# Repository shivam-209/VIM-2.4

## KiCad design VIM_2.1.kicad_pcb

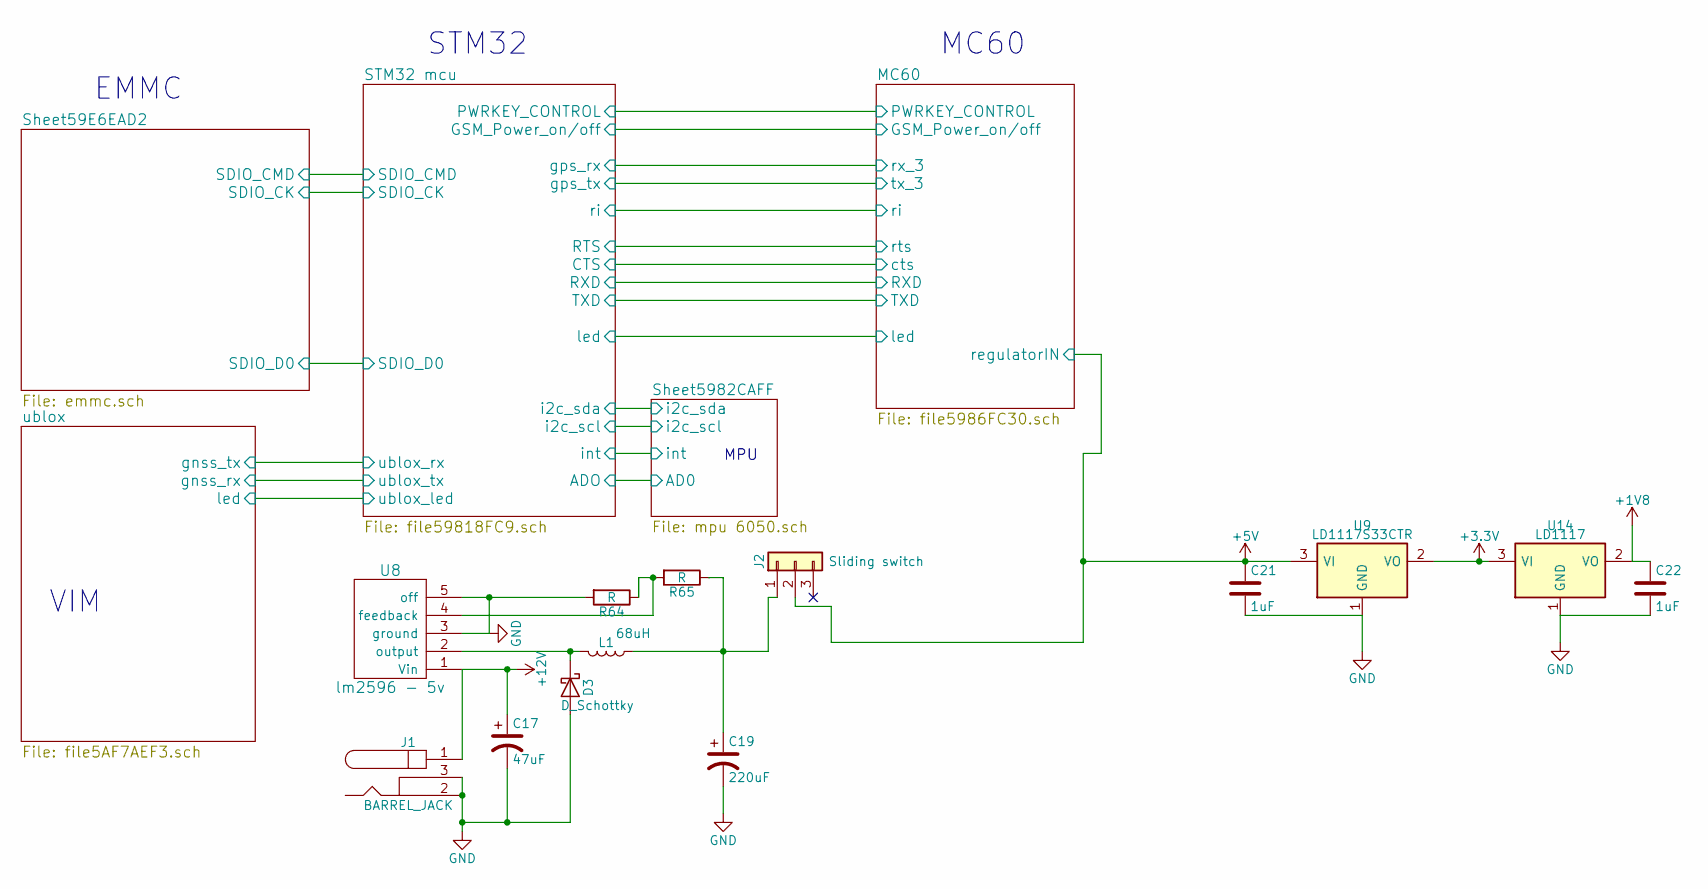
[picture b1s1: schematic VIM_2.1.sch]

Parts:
C17: 47uF; CP_Elec_8x6.7
C19: 220uF; CP_Elec_6.3x5.7
C21, C22: 1uF; C_0603_HandSoldering
D3: D_Schottky; D_SOD-123
J1: BARREL_JACK
J2: Sliding switch; Pin_Header_Straight_1x03_Pitch2.54mm
L1: 68uH; L_7.3x7.3_H3.5
R64, R65: R; R_0603_HandSoldering
U8: lm2596 - 5v; TO-263-5_TabPin3
U9: LD1117S33CTR; SOT-223-3Lead_TabPin2
U14: LD1117; SOT-223-3_TabPin2

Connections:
+1V8: C22.1, U14.2 (VO); also elsewhere on the board
+3V3: U9.2 (VO), U14.3 (VI); also elsewhere on the board
+5V: C21.1, J2.2, U9.3 (VI); also elsewhere on the board
+12V: C17.1, J1.1, U8.1 (Vin); also elsewhere on the board
GND: C17.2, C19.2, C21.2, C22.2, D3.2 (A), J1.2, J1.3, R64.2, U8.3 (ground), U8.5 (off), U9.1 (GND), U14.1 (GND); also elsewhere on the board
unnamed: C19.1, J2.1, L1.1, R65.1
unnamed: D3.1 (K), L1.2, U8.2 (output)
unnamed: R64.1, R65.2, U8.4 (feedback)

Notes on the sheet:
EMMC
STM32
MC60
MPU
VIM

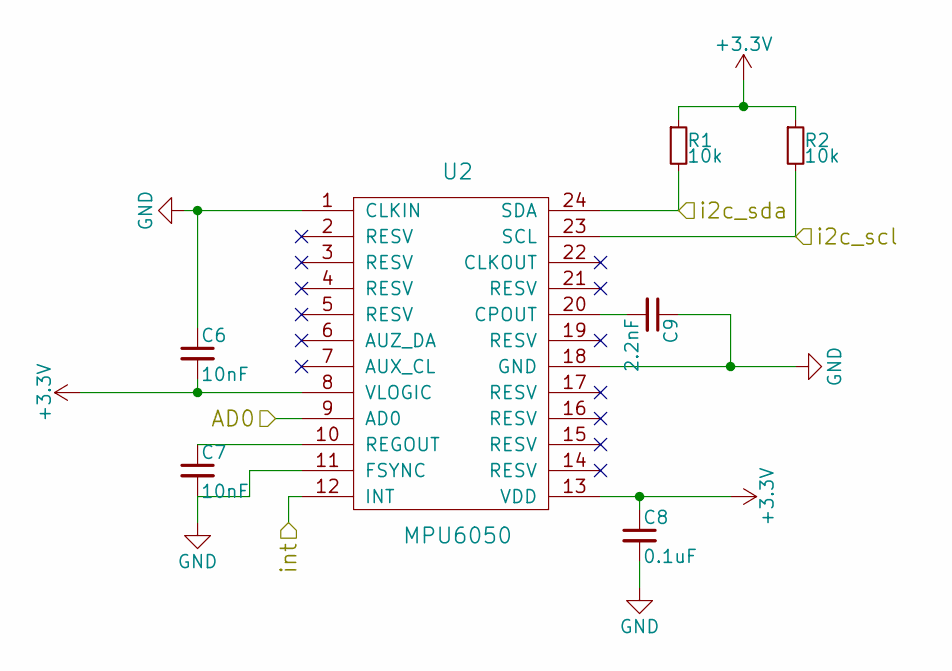
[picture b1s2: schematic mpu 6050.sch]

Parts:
C6, C7: 10nF; C_0603_HandSoldering
C8: 0.1uF; C_0603_HandSoldering
C9: 2.2nF; C_0603_HandSoldering
R1, R2: 10k; R_0603_HandSoldering
U2: MPU6050; QFN-24_4x4mm_Pitch0.5mm

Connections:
+3V3: C6.2, C8.1, R1.1, R2.1, U2.8 (VLOGIC), U2.13 (VDD); also elsewhere on the board
/STM32 mcu/i2c_scl: R2.2, U2.23 (SCL); also elsewhere on the board
/STM32 mcu/i2c_sda: R1.2, U2.24 (SDA); also elsewhere on the board
/STM32 mcu/int: U2.12 (INT); also elsewhere on the board
/Sheet5982CAFF/AD0: U2.9 (AD0); also elsewhere on the board
GND: C6.1, C7.2, C8.2, C9.1, U2.1 (CLKIN), U2.11 (FSYNC), U2.18 (GND); also elsewhere on the board
unnamed: C7.1, U2.10 (REGOUT)
unnamed: C9.2, U2.20 (CPOUT)

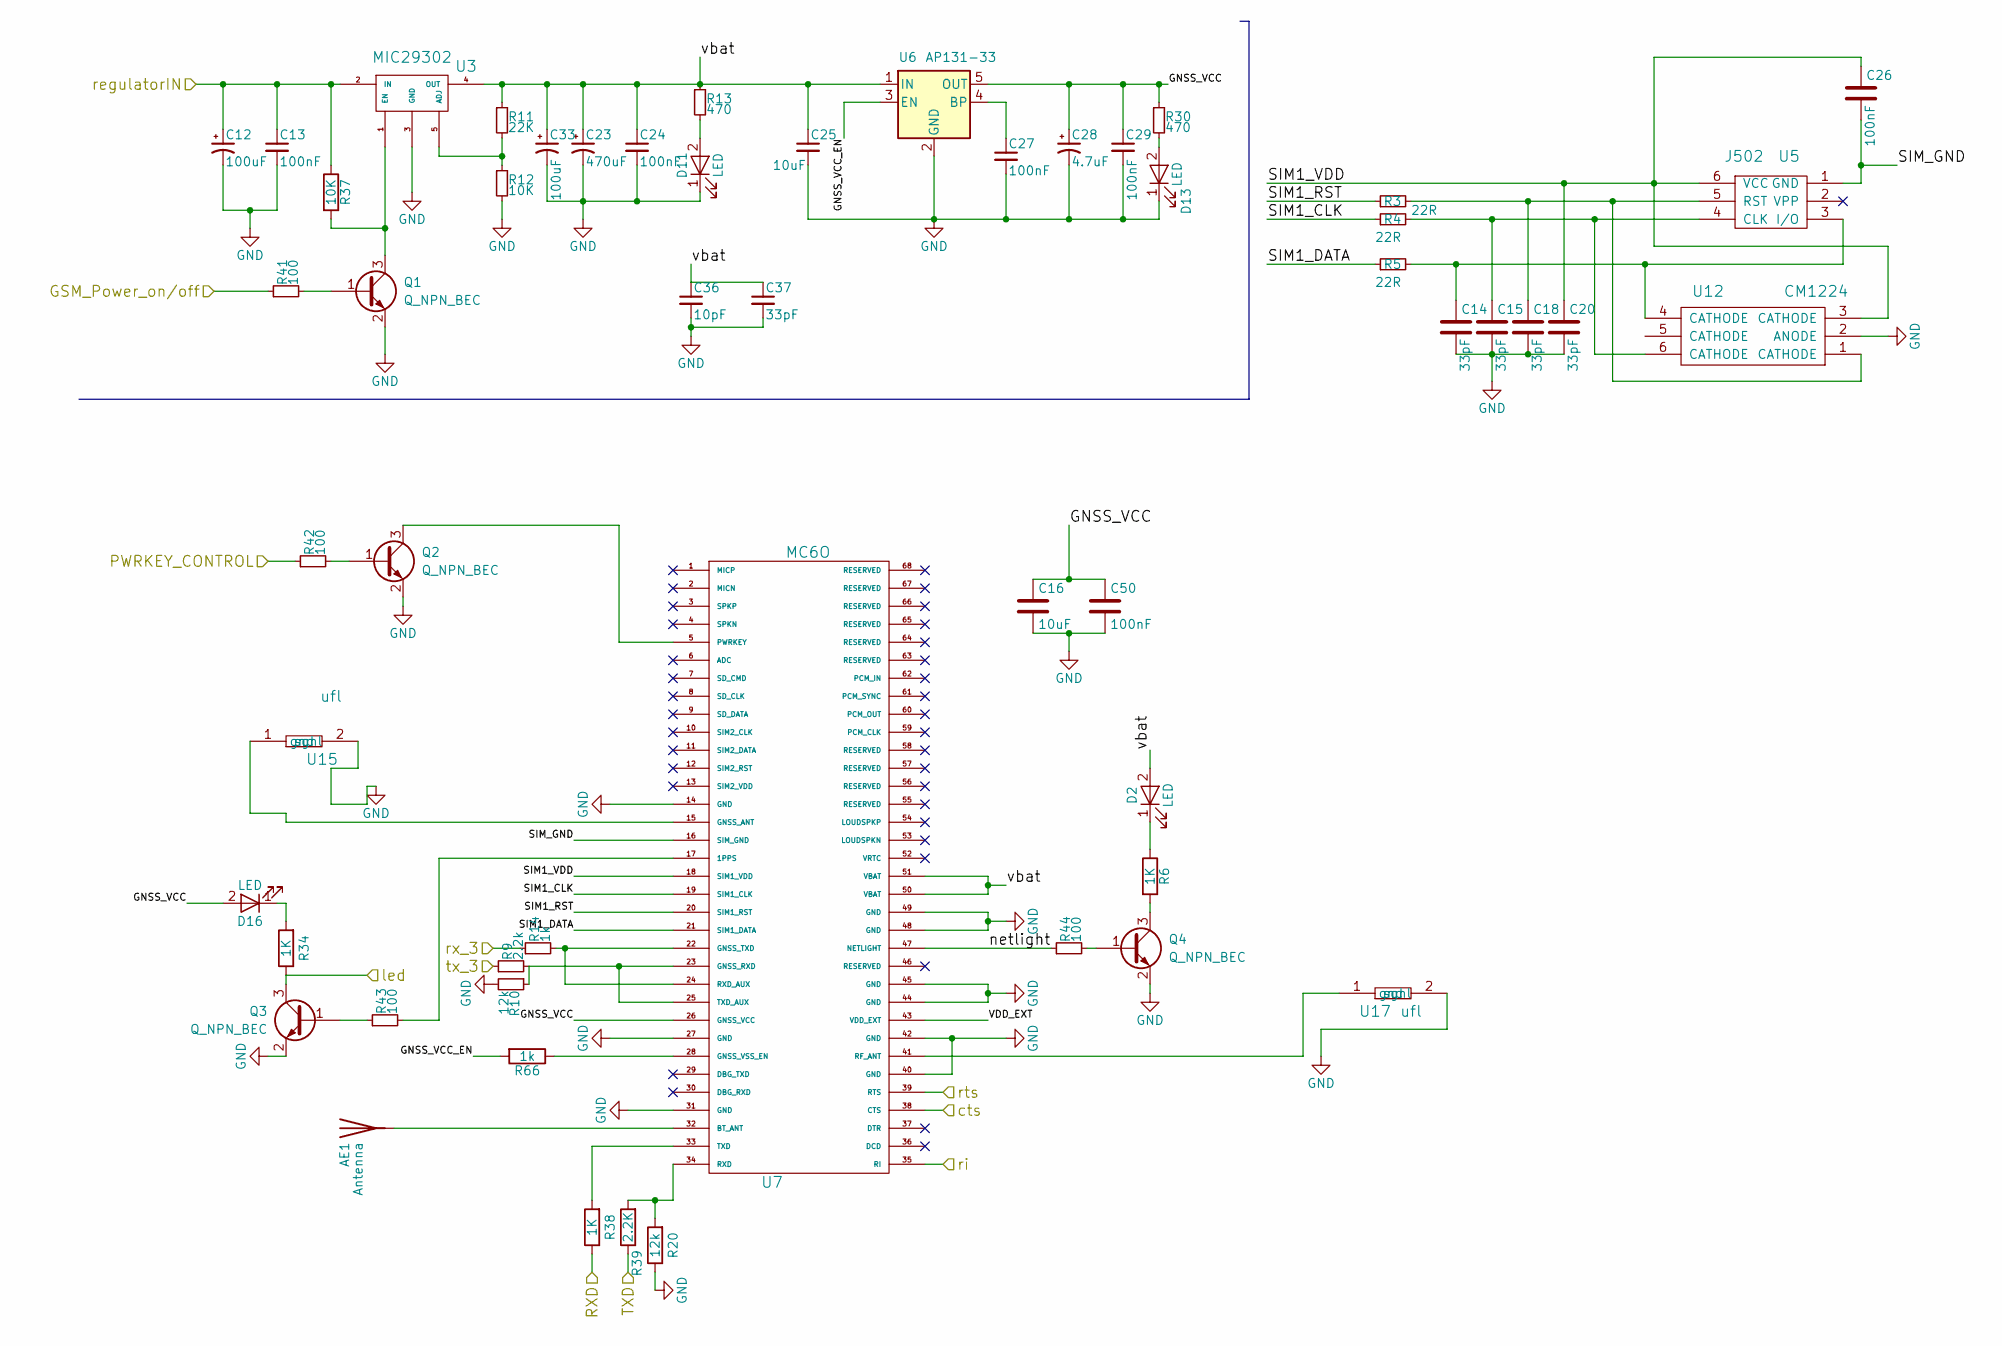
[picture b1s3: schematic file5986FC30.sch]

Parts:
AE1: Antenna; bluetooth_antenna
C12: 100uF; CP_Elec_6.3x5.7
C13, C24, C26, C27, C29, C50: 100nF; C_0603_HandSoldering
C14, C15, C18, C20, C37: 33pF; C_0603_HandSoldering
C16, C25: 10uF; C_0603_HandSoldering
C23: 470uF; CP_Elec_8x10
C28: 4.7uF; CP_Elec_5x5.3
C33: 100uF; CP_Tantalum_Case-D_EIA-7343-31_Reflow
C36: 10pF; C_0603_HandSoldering
D2, D11, D13, D16: LED; LED_0805
Q1, Q2, Q3, Q4: Q_NPN_BEC; SOT-23
R3, R4, R5: 22R; R_0603_HandSoldering
R6, R34, R38: 1K; R_0603_HandSoldering
R9: 2.2k; R_0603_HandSoldering
R10, R20: 12k; R_0603_HandSoldering
R11: 22K; R_0603_HandSoldering
R12, R37: 10K; R_0603_HandSoldering
R13, R30: 470; R_0603_HandSoldering
R14, R66: 1k; R_0603_HandSoldering
R39: 2.2K; R_0603_HandSoldering
R41, R42, R43, R44: 100; R_0603_HandSoldering
U3: MIC29302; TO-263-5_TabPin3
U5: J502; simcardconn
U6: AP131-33; SOT-23-5
U7: MC6O; Quectel_MC-60
U12: CM1224; SOT-23-6
U15, U17: ufl; ufl_shield

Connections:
+5V: C12.1, C13.1, R37.1, U3.2 (IN); also elsewhere on the board
/MC60/GNSS_VCC: C16.1, C28.1, C29.1, C50.1, D16.2 (A), R30.1, U6.5 (OUT), U7.26 (GNSS_VCC)
/MC60/GNSS_VCC_EN: R66.2, U6.3 (EN)
/MC60/GSM_Power_on/off: R41.1; also elsewhere on the board
/MC60/PWRKEY_CONTROL: R42.1; also elsewhere on the board
/MC60/RXD: R38.1; also elsewhere on the board
/MC60/SIM1_CLK: R4.1, U7.19 (SIM1_CLK)
/MC60/SIM1_DATA: R5.1, U7.21 (SIM1_DATA)
/MC60/SIM1_RST: R3.1, U7.20 (SIM1_RST)
/MC60/SIM1_VDD: C20.1, C26.1, U5.6 (VCC), U7.18 (SIM1_VDD), U12.3 (CATHODE)
/MC60/SIM_GND: C26.2, U5.1 (GND), U7.16 (SIM_GND)
/MC60/TXD: R39.1; also elsewhere on the board
/MC60/VDD_EXT: U7.43 (VDD_EXT)
/MC60/led: Q3.3 (C), R34.1; also elsewhere on the board
/MC60/netlight: R44.1, U7.47 (NETLIGHT)
/MC60/ri: U7.35 (RI); also elsewhere on the board
/MC60/vbat: C23.1, C24.1, C25.1, C33.1, C36.1, C37.1, D2.2 (A), R11.1, R13.1, U3.4 (OUT), U6.1 (IN), U7.50 (VBAT), U7.51 (VBAT)
/STM32 mcu/CTS: U7.38 (CTS); also elsewhere on the board
/STM32 mcu/RTS: U7.39 (RTS); also elsewhere on the board
/STM32 mcu/gps_rx: R14.1; also elsewhere on the board
/STM32 mcu/gps_tx: R9.1; also elsewhere on the board
GND: C12.2, C13.2, C14.2, C15.2, C16.2, C18.2, C20.2, C23.2, C24.2, C25.2, C27.2, C28.2, C29.2, C33.2, C36.2, C37.2, C50.2, D11.1 (K), D13.1 (K), Q1.2 (E), Q2.2 (E), Q3.2 (E), Q4.2 (E), R10.2, R12.2, R20.1, U3.3 (GND), U6.2 (GND), U7.14 (GND), U7.27 (GND), U7.31 (GND), U7.40 (GND), U7.42 (GND), U7.44 (GND), U7.45 (GND), U7.48 (GND), U7.49 (GND), U12.2 (ANODE), U15.2 (gnd), U17.2 (gnd); also elsewhere on the board
unnamed: AE1.1, U7.32 (BT_ANT)
unnamed: C14.1, R5.2, U5.3 (I/O), U12.4 (CATHODE)
unnamed: C15.1, R4.2, U5.4 (CLK), U12.6 (CATHODE)
unnamed: C18.1, R3.2, U5.5 (RST), U12.1 (CATHODE)
unnamed: C27.1, U6.4 (BP)
unnamed: D2.1 (K), R6.1
unnamed: D11.2 (A), R13.2
unnamed: D13.2 (A), R30.2
unnamed: D16.1 (K), R34.2
unnamed: Q1.1 (B), R41.2
unnamed: Q1.3 (C), R37.2, U3.1 (EN)
unnamed: Q2.1 (B), R42.2
unnamed: Q2.3 (C), U7.5 (PWRKEY)
unnamed: Q3.1 (B), R43.1
unnamed: Q4.1 (B), R44.2
unnamed: Q4.3 (C), R6.2
unnamed: R9.2, R10.1, U7.23 (GNSS_RXD), U7.25 (TXD_AUX)
unnamed: R11.2, R12.1, U3.5 (ADJ)
unnamed: R14.2, U7.22 (GNSS_TXD), U7.24 (RXD_AUX)
unnamed: R20.2, R39.2, U7.34 (RXD)
unnamed: R38.2, U7.33 (TXD)
unnamed: R43.2, U7.17 (1PPS)
unnamed: R66.1, U7.28 (GNSS_VSS_EN)
unnamed: U7.15 (GNSS_ANT), U15.1 (sgnl)
unnamed: U7.41 (RF_ANT), U17.1 (sgnl)

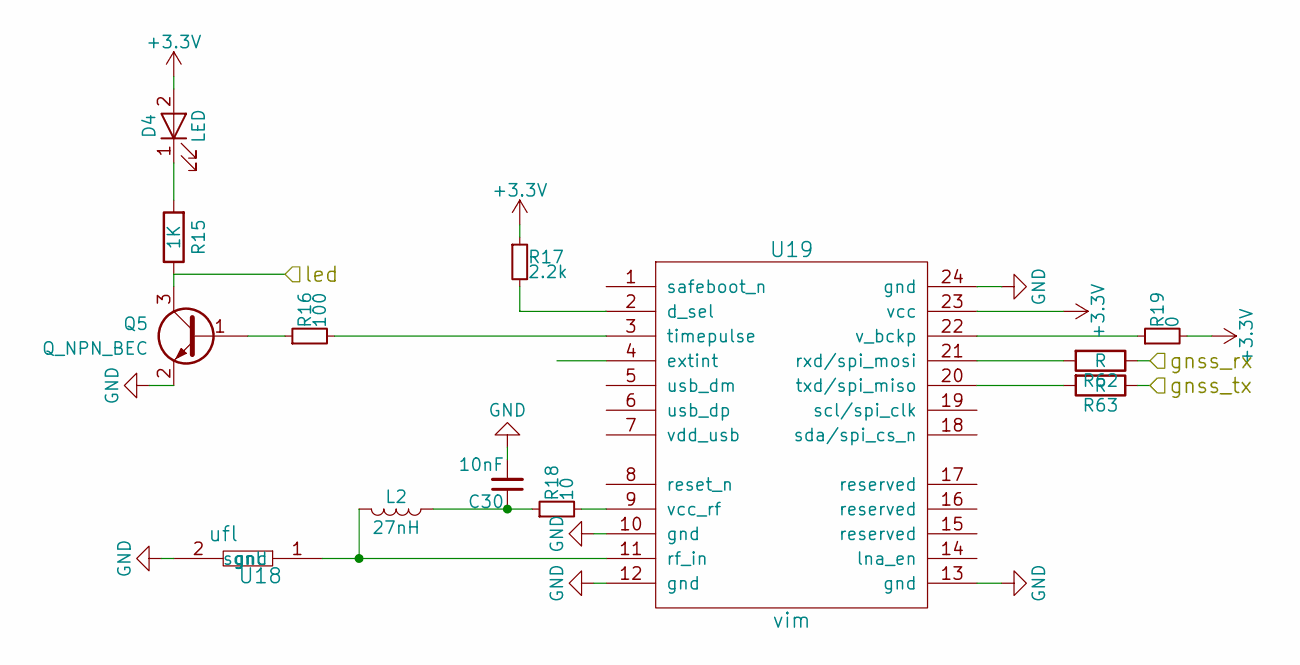
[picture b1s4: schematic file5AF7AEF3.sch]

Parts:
C30: 10nF; C_0603_HandSoldering
D4: LED; LED_0805
L2: 27nH; L_0805
Q5: Q_NPN_BEC; SOT-23
R15: 1K; R_0603_HandSoldering
R16: 100; R_0603_HandSoldering
R17: 2.2k; R_0603_HandSoldering
R18: 10; R_0603_HandSoldering
R19: 0; R_0603_HandSoldering
R62, R63: R; R_0603_HandSoldering
U18: ufl; ufl_shield
U19: vim; MU8

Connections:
+3V3: D4.2 (A), R17.1, R19.2, U19.23 (vcc); also elsewhere on the board
/ublox/gnss_rx: R62.1; also elsewhere on the board
/ublox/gnss_tx: R63.1; also elsewhere on the board
/ublox/led: Q5.3 (C), R15.1; also elsewhere on the board
GND: C30.2, Q5.2 (E), U18.2 (gnd), U19.10 (gnd), U19.12 (gnd), U19.13 (gnd), U19.24 (gnd); also elsewhere on the board
unnamed: C30.1, L2.1, R18.1
unnamed: D4.1 (K), R15.2
unnamed: L2.2, U18.1 (sgnl), U19.11 (rf_in)
unnamed: Q5.1 (B), R16.1
unnamed: R16.2, U19.3 (timepulse)
unnamed: R17.2, U19.2 (d_sel)
unnamed: R18.2, U19.9 (vcc_rf)
unnamed: R19.1, U19.22 (v_bckp)
unnamed: R62.2, U19.21 (rxd/spi_mosi)
unnamed: R63.2, U19.20 (txd/spi_miso)

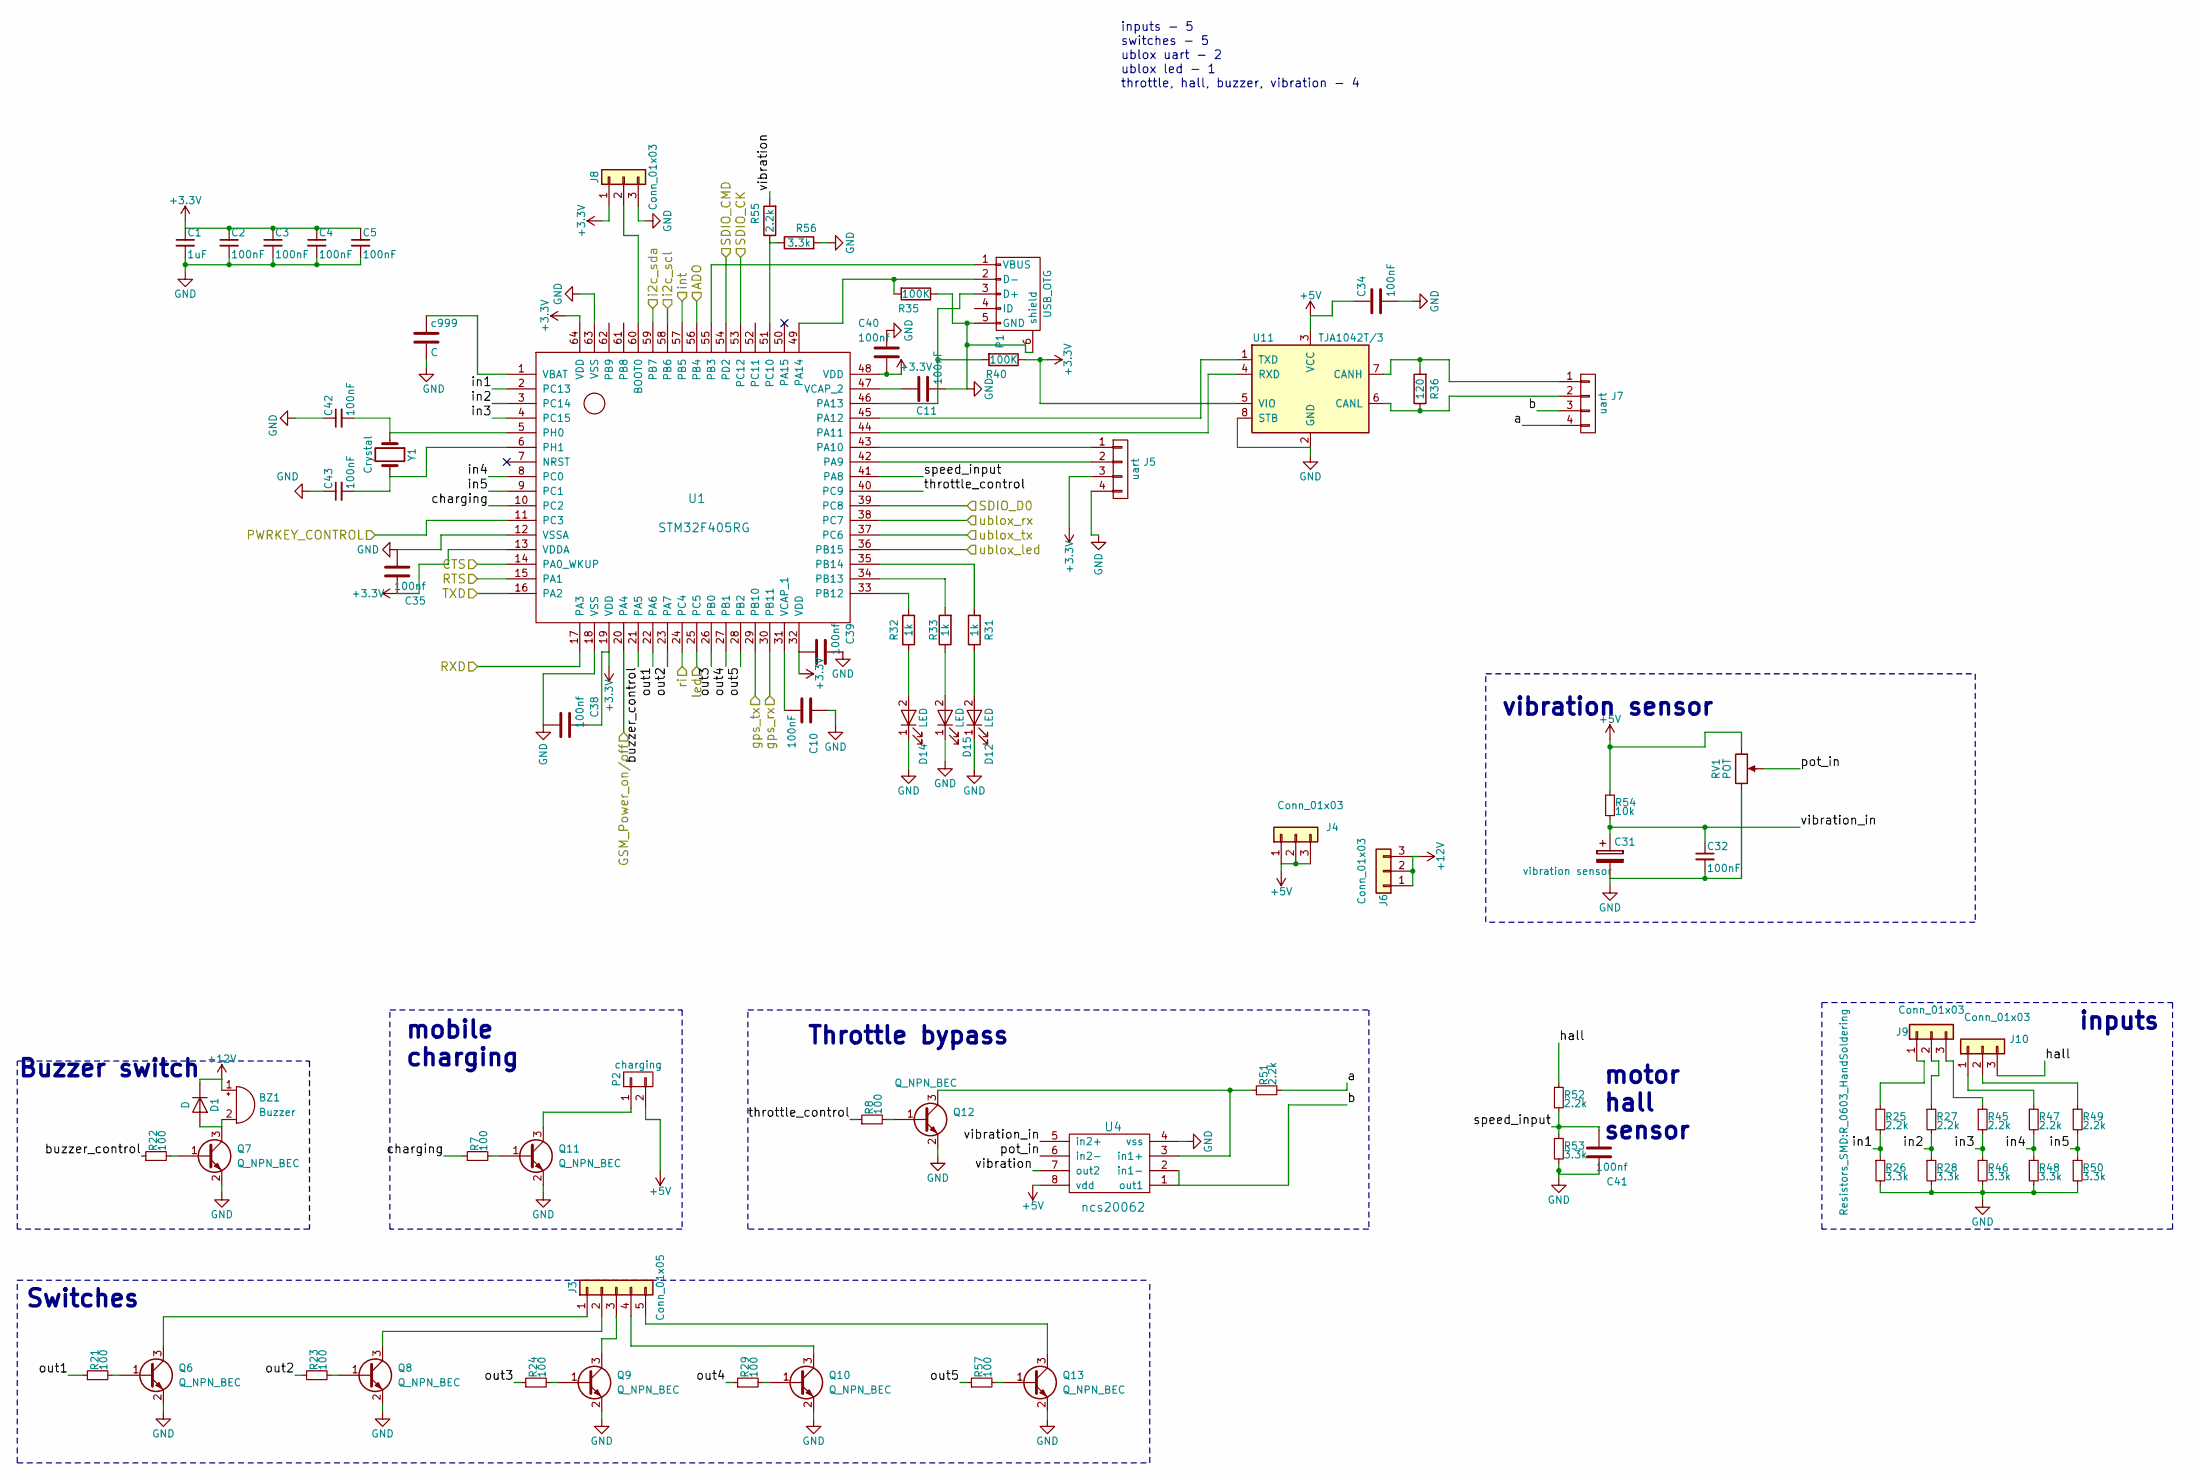
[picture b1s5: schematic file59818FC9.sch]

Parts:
BZ1: Buzzer; Buzzer_12x9.5RM7.6
C1: 1uF; C_0603_HandSoldering
C2, C3, C4, C5, C10, C11, C32, C34, C42, C43: 100nF; C_0603_HandSoldering
C31: vibration sensor; CP_Radial_D5.0mm_P2.50mm
C35, C38, C39, C40, C41: 100nf; C_0603_HandSoldering
D1: D; D_SOD-123
D12, D14, D15: LED; LED_0805
J3: Conn_01x05; Pin_Header_Straight_1x05_Pitch2.54mm
J4, J6, J8, J9, J10: Conn_01x03; Pin_Header_Straight_1x03_Pitch2.54mm
J5, J7: uart; Pin_Header_Straight_1x04_Pitch2.54mm
P1: USB_OTG; USB_Micro-B
P2: charging; Pin_Header_Straight_1x02_Pitch2.54mm
Q6, Q7, Q8, Q9, Q10, Q11, Q12, Q13: Q_NPN_BEC; SOT-23
R7, R8, R21, R22, R23, R24, R29, R57: 100; R_0603_HandSoldering
R25, R27, R45, R47, R49, R51, R52, R55: 2.2k; R_0603_HandSoldering
R26, R28, R46, R48, R50, R53, R56: 3.3k; R_0603_HandSoldering
R31, R32, R33: 1k; R_0603_HandSoldering
R35, R40: 100K; R_0603_HandSoldering
R36: 120; R_0603_HandSoldering
R54: 10k; R_0603_HandSoldering
RV1: POT; Potentiometer_Triwood_RM-065
U1: STM32F405RG; LQFP-64_10x10mm_Pitch0.5mm
U4: ncs20062; SOIC-8_3.9x4.9mm_Pitch1.27mm
U11: TJA1042T/3; SOIC-8_3.9x4.9mm_Pitch1.27mm
Y1: Crystal; Crystal_HC52-8mm_Vertical
c999: C; C_0603_HandSoldering

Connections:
+3V3: C1.1, C2.1, C3.1, C4.1, C5.1, C35.1, C38.1, C39.2, C40.2, J5.3, J8.1, R40.1, U1.13 (VDDA), U1.19 (VDD), U1.32 (VDD), U1.48 (VDD), U1.64 (VDD), U11.5 (VIO); also elsewhere on the board
+5V: C34.1, J4.1, J4.2, J4.3, P2.2, R54.1, RV1.1, U4.8 (vdd), U11.3 (VCC); also elsewhere on the board
+12V: BZ1.1 (-), D1.1 (K), J6.1, J6.2, J6.3; also elsewhere on the board
/MC60/GSM_Power_on/off: U1.20 (PA4); also elsewhere on the board
/MC60/PWRKEY_CONTROL: U1.11 (PC3); also elsewhere on the board
/MC60/RXD: U1.17 (PA3); also elsewhere on the board
/MC60/TXD: U1.16 (PA2); also elsewhere on the board
/MC60/led: U1.25 (PC5); also elsewhere on the board
/MC60/ri: U1.24 (PC4); also elsewhere on the board
/STM32 mcu/CTS: U1.14 (PA0_WKUP); also elsewhere on the board
/STM32 mcu/RTS: U1.15 (PA1); also elsewhere on the board
/STM32 mcu/SDIO_CK: U1.53 (PC12); also elsewhere on the board
/STM32 mcu/SDIO_CMD: U1.54 (PD2); also elsewhere on the board
/STM32 mcu/SDIO_D0: U1.39 (PC8); also elsewhere on the board
/STM32 mcu/a: J7.4, R51.2
/STM32 mcu/b: J7.3, U4.1 (out1), U4.2 (in1-)
/STM32 mcu/buzzer_control: R22.1, U1.21 (PA5)
/STM32 mcu/charging: R7.1, U1.10 (PC2)
/STM32 mcu/gps_rx: U1.30 (PB11); also elsewhere on the board
/STM32 mcu/gps_tx: U1.29 (PB10); also elsewhere on the board
/STM32 mcu/hall: J10.3, R52.1
/STM32 mcu/i2c_scl: U1.58 (PB6); also elsewhere on the board
/STM32 mcu/i2c_sda: U1.59 (PB7); also elsewhere on the board
/STM32 mcu/in1: R25.2, R26.1, U1.2 (PC13)
/STM32 mcu/in2: R27.2, R28.1, U1.3 (PC14)
/STM32 mcu/in3: R45.2, R46.1, U1.4 (PC15)
/STM32 mcu/in4: R47.2, R48.1, U1.8 (PC0)
/STM32 mcu/in5: R49.2, R50.1, U1.9 (PC1)
/STM32 mcu/int: U1.57 (PB5); also elsewhere on the board
/STM32 mcu/out1: R21.1, U1.22 (PA6)
/STM32 mcu/out2: R23.1, U1.23 (PA7)
/STM32 mcu/out3: R24.1, U1.26 (PB0)
/STM32 mcu/out4: R29.1, U1.27 (PB1)
/STM32 mcu/out5: R57.1, U1.28 (PB2)
/STM32 mcu/pot_in: RV1.2, U4.6 (in2-)
/STM32 mcu/speed_input: C41.2, R52.2, R53.1, U1.41 (PA8)
/STM32 mcu/throttle_control: R8.1, U1.40 (PC9)
/STM32 mcu/vibration: R55.2, U4.7 (out2)
/STM32 mcu/vibration_in: C31.1, C32.1, R54.2, U4.5 (in2+)
/Sheet5982CAFF/AD0: U1.56 (PB4); also elsewhere on the board
/ublox/gnss_rx: U1.37 (PC6); also elsewhere on the board
/ublox/gnss_tx: U1.38 (PC7); also elsewhere on the board
/ublox/led: U1.36 (PB15); also elsewhere on the board
GND: C1.2, C2.2, C3.2, C4.2, C5.2, C10.1, C11.2, C31.2, C32.2, C34.2, C35.2, C38.2, C39.1, C40.1, C41.1, C42.1, C43.1, D12.1 (K), D14.1 (K), D15.1 (K), J5.4, J8.3, P1.5 (GND), P1.6 (shield), Q6.2 (E), Q7.2 (E), Q8.2 (E), Q9.2 (E), Q10.2 (E), Q11.2 (E), Q12.2 (E), Q13.2 (E), R26.2, R28.2, R35.1, R46.2, R48.2, R50.2, R53.2, R56.2, RV1.3, U1.12 (VSSA), U1.18 (VSS), U1.63 (VSS), U4.4 (vss), U11.2 (GND), U11.8 (STB), c999.2; also elsewhere on the board
unnamed: BZ1.2 (+), D1.2 (A), Q7.3 (C)
unnamed: C10.2, U1.31 (VCAP_1)
unnamed: C11.1, U1.47 (VCAP_2)
unnamed: C42.2, U1.5 (PH0), Y1.1
unnamed: C43.2, U1.6 (PH1), Y1.2
unnamed: D12.2 (A), R31.1
unnamed: D14.2 (A), R32.2
unnamed: D15.2 (A), R33.1
unnamed: J3.1, Q6.3 (C)
unnamed: J3.2, Q8.3 (C)
unnamed: J3.3, Q9.3 (C)
unnamed: J3.4, Q10.3 (C)
unnamed: J3.5, Q13.3 (C)
unnamed: J5.1, U1.43 (PA10)
unnamed: J5.2, U1.42 (PA9)
unnamed: J7.1, R36.2, U11.7 (CANH)
unnamed: J7.2, R36.1, U11.6 (CANL)
unnamed: J8.2, U1.60 (BOOT0)
unnamed: J9.1, R25.1
unnamed: J9.2, R27.1
unnamed: J9.3, R45.1
unnamed: J10.1, R47.1
unnamed: J10.2, R49.1
unnamed: P1.1 (VBUS), U1.55 (PB3)
unnamed: P1.2 (D-), R35.2, U1.49 (PA14)
unnamed: P1.3 (D+), R40.2, U1.46 (PA13)
unnamed: P2.1, Q11.3 (C)
unnamed: Q6.1 (B), R21.2
unnamed: Q7.1 (B), R22.2
unnamed: Q8.1 (B), R23.2
unnamed: Q9.1 (B), R24.2
unnamed: Q10.1 (B), R29.2
unnamed: Q11.1 (B), R7.2
unnamed: Q12.1 (B), R8.2
unnamed: Q12.3 (C), R51.1, U4.3 (in1+)
unnamed: Q13.1 (B), R57.2
unnamed: R31.2, U1.35 (PB14)
unnamed: R32.1, U1.33 (PB12)
unnamed: R33.2, U1.34 (PB13)
unnamed: R55.1, R56.1, U1.51 (PC10)
unnamed: U1.1 (VBAT), c999.1
unnamed: U1.44 (PA11), U11.4 (RXD)
unnamed: U1.45 (PA12), U11.1 (TXD)

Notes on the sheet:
inputs - 5 switches - 5 ublox uart - 2 ublox led - 1 throttle, hall, buzzer, vibration - 4
Buzzer switch
Switches
mobile charging
Throttle bypass
vibration sensor
inputs
motor hall sensor

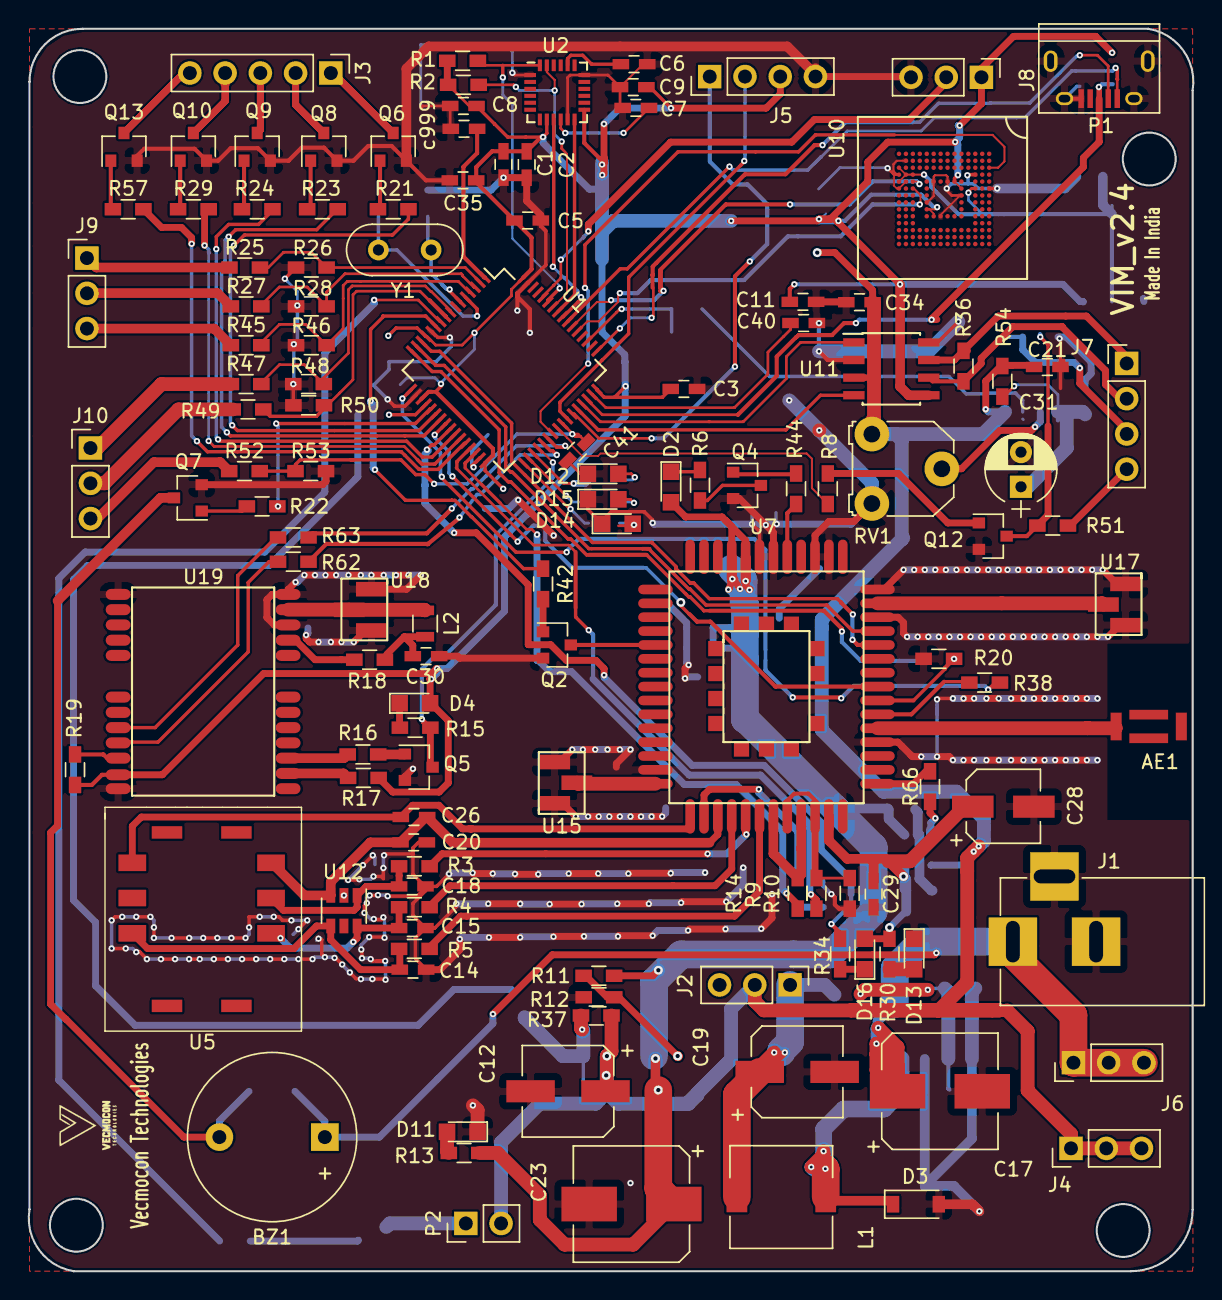
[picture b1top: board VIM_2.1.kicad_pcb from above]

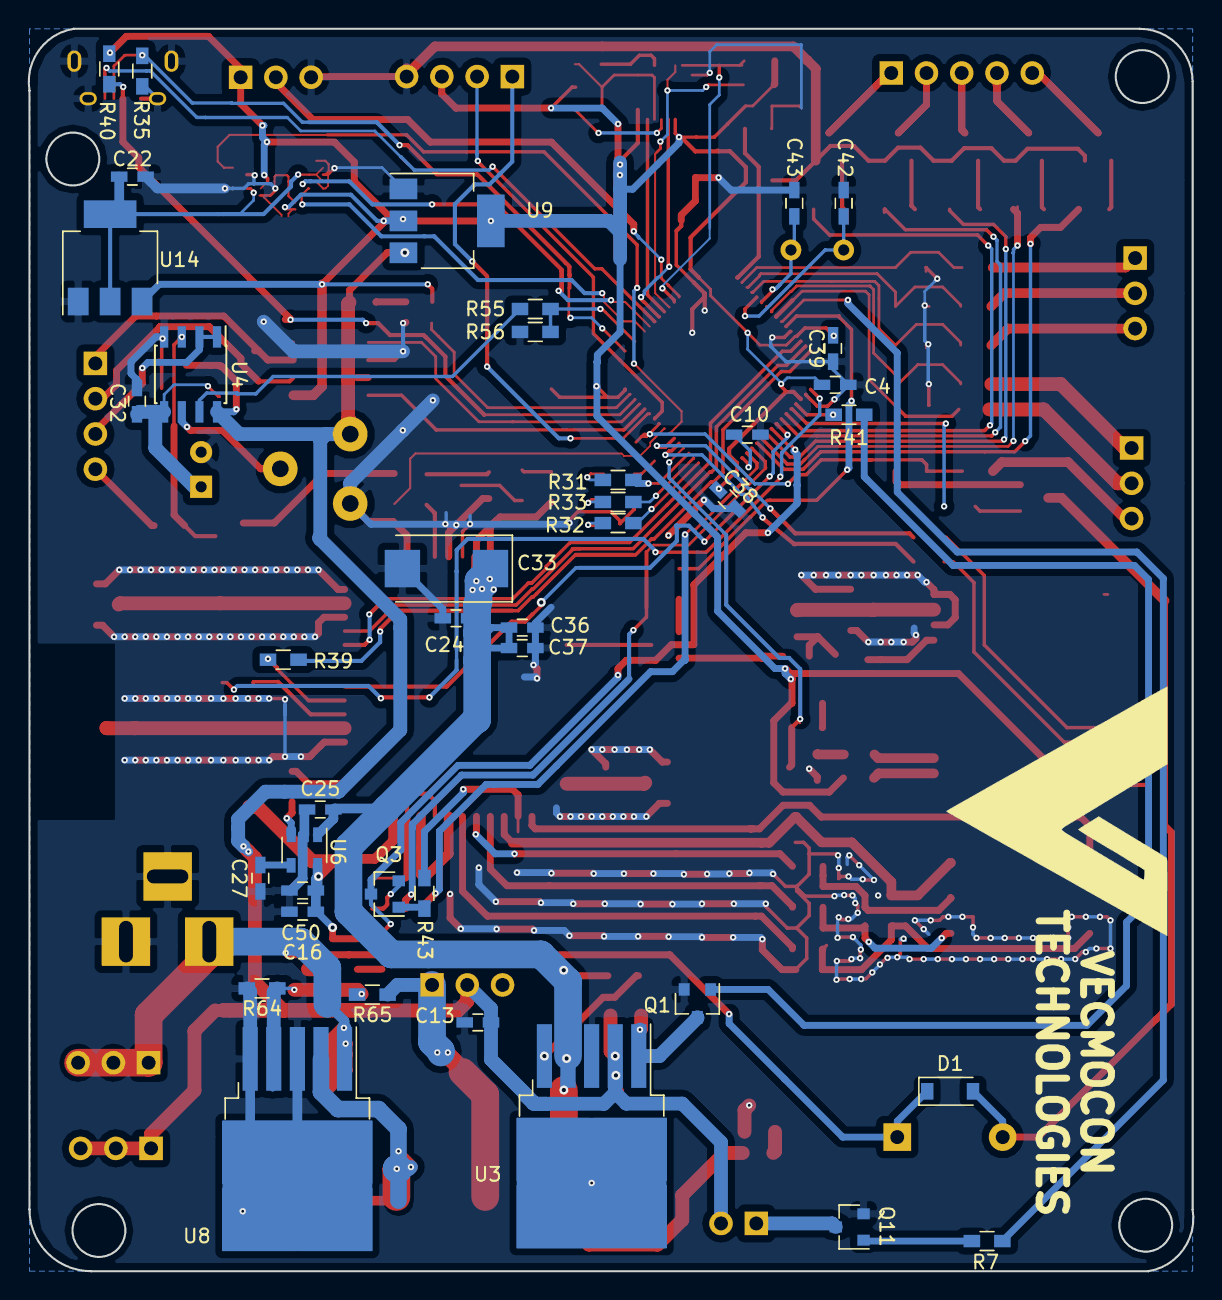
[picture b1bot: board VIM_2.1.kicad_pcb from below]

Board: 2 copper layers, 83.9 x 89.5 mm, 165 parts (40 on the bottom side), 137 nets.

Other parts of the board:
U10: emmc; eMMC2.4

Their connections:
+1V8: U10.36, U10.37, U10.38, U10.39, U10.40; also elsewhere on the board
+3V3: U10.32, U10.33, U10.34, U10.35; also elsewhere on the board
/STM32 mcu/SDIO_CK: U10.50; also elsewhere on the board
/STM32 mcu/SDIO_CMD: U10.49; also elsewhere on the board
/STM32 mcu/SDIO_D0: U10.1; also elsewhere on the board
GND: U10.21, U10.22, U10.23, U10.24, U10.25, U10.26, U10.27, U10.28, U10.29, U10.30, U10.31; also elsewhere on the board

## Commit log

2018-06-08 kicad files added
    added kicad project
2018-06-09 added text
    added sushil changes
2018-06-09 added shivam changes text
2018-06-09 changes to b
2018-06-09 Revert "changes to b"
    This reverts commit 29845ce44828af67f545c5cae162d888299830da.
2018-06-19 Final pcb given to pcbpower
    fleet management vim with following features
    - ublox m8u, mc60
    - mpu6050
    - vibration sensor
    - buzzer, switches, thottle bypass,
    - sim interface according to quectel
2018-07-28 pcb print 28 jul
2018-07-28 final
2018-07-28 PCB SENT TO PCB POWER
